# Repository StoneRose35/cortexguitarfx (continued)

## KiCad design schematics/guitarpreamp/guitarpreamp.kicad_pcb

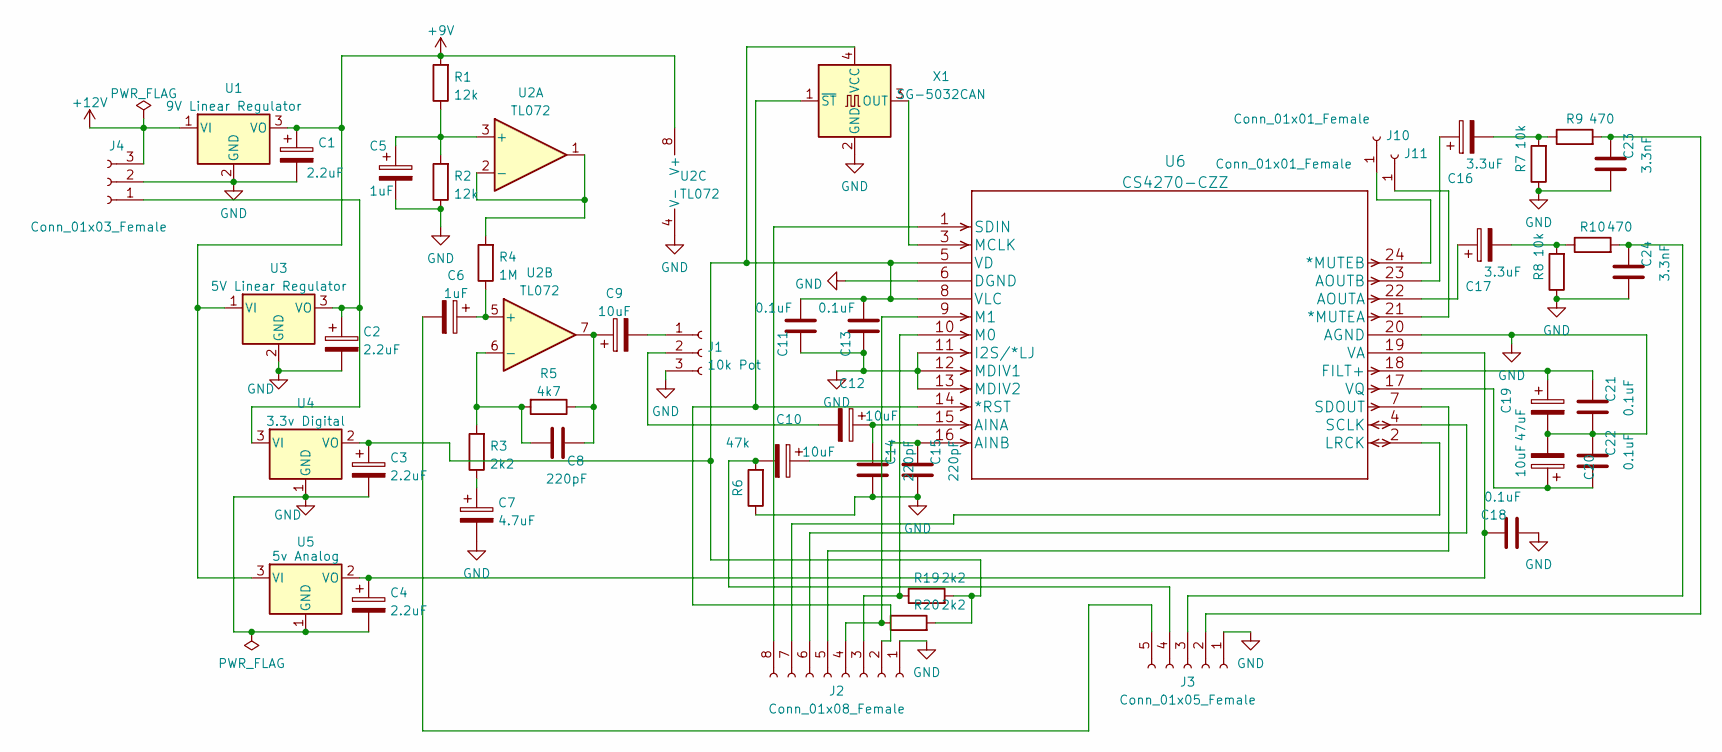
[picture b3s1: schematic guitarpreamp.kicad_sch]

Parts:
C1, C2, C3, C4: 2.2uF; CP_Elec_4x4.5
C5, C6: 1uF; CP_Elec_4x4.5
C7: 4.7uF; CP_Elec_4x4.5
C8, C14, C15: 220pF; C_0603_1608Metric_Pad1.08x0.95mm_HandSolder
C9, C10, C12, C20: 10uF; CP_Elec_4x4.5
C11, C13, C18, C21, C22: 0.1uF; C_1210_3225Metric_Pad1.33x2.70mm_HandSolder
C16, C17: 3.3uF; CP_Elec_4x4.5
C19: 47uF; CP_Elec_5x5.4
C23, C24: 3.3nF; C_0805_2012Metric_Pad1.18x1.45mm_HandSolder
J1: 10k Pot; PinHeader_1x03_P2.54mm_Vertical
J2: Conn_01x08_Female; PinHeader_1x08_P2.54mm_Vertical
J3: Conn_01x05_Female; PinHeader_1x05_P2.54mm_Vertical
J4: Conn_01x03_Female; PinHeader_1x03_P2.54mm_Vertical
J10, J11: Conn_01x01_Female; Pin_D0.7mm_L6.5mm_W1.8mm_FlatFork
R1, R2: 12k; R_0603_1608Metric_Pad0.98x0.95mm_HandSolder
R3, R19, R20: 2k2; R_0603_1608Metric_Pad0.98x0.95mm_HandSolder
R4: 1M; R_0603_1608Metric_Pad0.98x0.95mm_HandSolder
R5: 4k7; R_0603_1608Metric_Pad0.98x0.95mm_HandSolder
R6: 47k; R_0603_1608Metric_Pad0.98x0.95mm_HandSolder
R7, R8: 10k; R_0603_1608Metric_Pad0.98x0.95mm_HandSolder
R9, R10: 470; R_0603_1608Metric_Pad0.98x0.95mm_HandSolder
U1: 9V Linear Regulator; TO-252-2
U2: TL072; SOIC-8_3.9x4.9mm_P1.27mm
U3: 5V Linear Regulator; TO-252-2
U4: 3.3v Digital; SOT-23
U5: 5v Analog; SOT-23
U6: CS4270-CZZ; TSSOP-24_4.4x7.8mm_P0.65mm
X1: SG-5032CAN; Oscillator_SMD_SeikoEpson_SG8002CA-4Pin_7.0x5.0mm_HandSolde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

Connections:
+9V: C1.1, R1.2, U1.3 (VO), U2.8 (V+), U3.1 (VI), U5.3 (VI)
+12V: J4.3, U1.1 (VI)
GND: C1.2, C2.2, C3.2, C4.2, C5.2, C7.2, C11.2, C13.2, C14.1, C15.1, C18.1, C19.2, C20.2, C21.1, C22.2, C23.1, C24.1, J1.3, J2.1, J3.1, J4.2, R2.1, R6.1, R7.1, R8.1, U1.2 (GND), U2.4 (V-), U3.2 (GND), U4.1 (GND), U5.1 (GND), U6.6 (DGND), U6.11 (I2S/*LJ), U6.12 (MDIV1), U6.13 (MDIV2), U6.20 (AGND), X1.2 (GND)
unnamed: C2.1, J4.1, U3.3 (VO), U4.3 (VI)
unnamed: C5.1, R1.1, R2.2, U2.3 (+)
unnamed: C6.1, R4.1, U2.5 (+)
unnamed: C6.2, J3.5
unnamed: C7.1, R3.1
unnamed: C8.1, R3.2, R5.2, U2.6 (-)
unnamed: C8.2, C9.1, R5.1, U2.7
unnamed: C9.2, J1.1
unnamed: C10.1, C15.2, U6.16 (AINB)
unnamed: C10.2, J3.4, R6.2
unnamed: C3.1, C11.1, C13.1, R19.2, R20.2, U4.2 (VO), U6.5 (VD), U6.8 (VLC), X1.4 (VCC)
unnamed: C12.1, C14.2, U6.15 (AINA)
unnamed: C12.2, J1.2
unnamed: C16.1, U6.23 (AOUTB)
unnamed: C16.2, R7.2, R9.1
unnamed: C17.1, U6.22 (AOUTA)
unnamed: C17.2, R8.2, R10.1
unnamed: C4.1, C18.2, U5.2 (VO), U6.19 (VA)
unnamed: C19.1, C21.2, U6.18 (FILT+)
unnamed: C20.1, C22.1, U6.17 (VQ)
unnamed: C23.2, J3.2, R9.2
unnamed: C24.2, J3.3, R10.2
unnamed: J2.2, U6.14 (*RST), X1.1 (~ST)
unnamed: J2.3, R19.1, U6.10 (M0)
unnamed: J2.4, R20.1, U6.9 (M1)
unnamed: J2.5, U6.7 (SDOUT)
unnamed: J2.6, U6.4 (SCLK)
unnamed: J2.7, U6.2 (LRCK)
unnamed: J2.8, U6.1 (SDIN)
unnamed: J10.1, U6.24 (*MUTEB)
unnamed: J11.1, U6.21 (*MUTEA)
unnamed: R4.2, U2.1, U2.2 (-)
unnamed: U6.3 (MCLK), X1.3 (OUT)

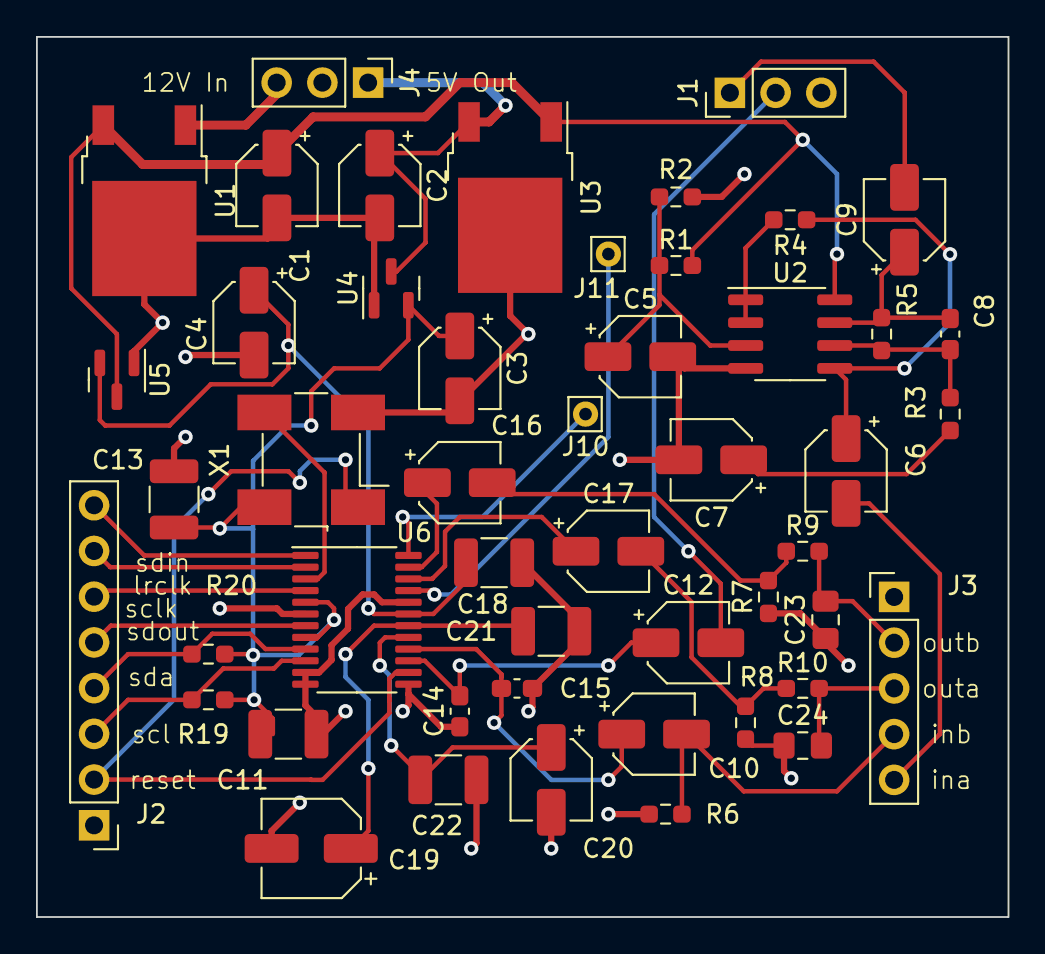
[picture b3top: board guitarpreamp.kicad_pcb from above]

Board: 2 copper layers, 54.0 x 48.9 mm, 49 parts (0 on the bottom side), 36 nets.

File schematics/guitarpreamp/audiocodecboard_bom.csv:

"Ref","Qnty","Value","Cmp name","Footprint","Description","Vendor"
"C1, C2, C3, C4, ","4","2.2uF","C_Polarized","Capacitor_SMD:CP_Elec_4x4.5","Polarized capacitor",""
"C5, C6, ","2","1uF","C_Polarized","Capacitor_SMD:CP_Elec_4x4.5","Polarized capacitor",""
"C7, ","1","4.7uF","C_Polarized","Capacitor_SMD:CP_Elec_4x4.5","Polarized capacitor",""
"C8, C14, C15, ","3","220pF","C","Capacitor_SMD:C_0603_1608Metric_Pad1.08x0.95mm_HandSolder","Unpolarized capacitor",""
"C9, C10, C12, C20, ","4","10uF","C_Polarized","Capacitor_SMD:CP_Elec_4x4.5","Polarized capacitor",""
"C11, C13, C18, C21, C22, ","5","0.1uF","C","Capacitor_SMD:C_1210_3225Metric_Pad1.33x2.70mm_HandSolder","Unpolarized capacitor",""
"C16, C17, ","2","3.3uF","C_Polarized","Capacitor_SMD:CP_Elec_4x4.5","Polarized capacitor",""
"C19, ","1","47uF","C_Polarized","Capacitor_SMD:CP_Elec_5x5.4","Polarized capacitor",""
"C23, C24, ","2","3.3nF","C","Capacitor_SMD:C_0805_2012Metric_Pad1.18x1.45mm_HandSolder","Unpolarized capacitor",""
"J1, ","1","10k Pot","Conn_01x03_Female","Connector_PinHeader_2.54mm:PinHeader_1x03_P2.54mm_Vertical","Generic connector, single row, 01x03, script generated (kicad-library-utils/schlib/autogen/connector/)",""
"J2, ","1","Conn_01x08_Female","Conn_01x08_Female","Connector_PinHeader_2.54mm:PinHeader_1x08_P2.54mm_Vertical","Generic connector, single row, 01x08, script generated (kicad-library-utils/schlib/autogen/connector/)",""
"J3, ","1","Conn_01x05_Female","Conn_01x05_Female","Connector_PinHeader_2.54mm:PinHeader_1x05_P2.54mm_Vertical","Generic connector, single row, 01x05, script generated (kicad-library-utils/schlib/autogen/connector/)",""
"J4, ","1","Conn_01x03_Female","Conn_01x03_Female","Connector_PinHeader_2.54mm:PinHeader_1x03_P2.54mm_Vertical","Generic connector, single row, 01x03, script generated (kicad-library-utils/schlib/autogen/connector/)",""
"J10, J11, ","2","Conn_01x01_Female","Conn_01x01_Female","Connector_Pin:Pin_D0.7mm_L6.5mm_W1.8mm_FlatFork","Generic connector, single row, 01x01, script generated (kicad-library-utils/schlib/autogen/connector/)",""
"R1, R2, ","2","12k","R","Resistor_SMD:R_0603_1608Metric_Pad0.98x0.95mm_HandSolder","Resistor",""
"R3, R19, R20, ","3","2k2","R","Resistor_SMD:R_0603_1608Metric_Pad0.98x0.95mm_HandSolder","Resistor",""
"R4, ","1","1M","R","Resistor_SMD:R_0603_1608Metric_Pad0.98x0.95mm_HandSolder","Resistor",""
"R5, ","1","4k7","R","Resistor_SMD:R_0603_1608Metric_Pad0.98x0.95mm_HandSolder","Resistor",""
"R6, ","1","47k","R","Resistor_SMD:R_0603_1608Metric_Pad0.98x0.95mm_HandSolder","Resistor",""
"R7, R8, ","2","10k","R","Resistor_SMD:R_0603_1608Metric_Pad0.98x0.95mm_HandSolder","Resistor",""
"R9, R10, ","2","470","R","Resistor_SMD:R_0603_1608Metric_Pad0.98x0.95mm_HandSolder","Resistor",""
"U1, ","1","9V Linear Regulator","LM78M05_TO252","Package_TO_SOT_SMD:TO-252-2","Positive 500mA 35V Linear Regulator, Fixed Output 5V, TO-252 (D-PAK)",""
"U2, ","1","TL072","TL072","Package_SO:SOIC-8_3.9x4.9mm_P1.27mm","Dual Low-Noise JFET-Input Operational Amplifiers, DIP-8/SOIC-8",""
"U3, ","1","5V Linear Regulator","LM78M05_TO252","Package_TO_SOT_SMD:TO-252-2","Positive 500mA 35V Linear Regulator, Fixed Output 5V, TO-252 (D-PAK)",""
"U4, ","1","3.3v Digital","MCP1700-1202E_SOT23","Package_TO_SOT_SMD:SOT-23","250mA Low Quiscent Current LDO, 1.2V output, SOT-23",""
"U5, ","1","5v Analog","MCP1700-1202E_SOT23","Package_TO_SOT_SMD:SOT-23","250mA Low Quiscent Current LDO, 1.2V output, SOT-23",""
"U6, ","1","CS4270-CZZ","CS4270-CZZ","Package_SO:TSSOP-24_4.4x7.8mm_P0.65mm","",""
"X1, ","1","SG-5032CAN","SG-5032CAN","Oscillator:Oscillator_SMD_SeikoEpson_SG8002CA-4Pin_7.0x5.0mm_HandSoldering","CMOS Clock Oscillator 1 to 75 MHz",""

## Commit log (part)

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2023-11-13 (hopefully) corrected level 2 layout
2023-11-14 increased initial delay for simple chorus
2023-11-14 fixed acoustic processor and included it
    instead of the mostercrusher
2023-11-17 fixed display error in ui lvl 1 and 2
2023-11-20 re-added component values previously lost due to kicad mishap
2023-11-23 more rearranging includes
2023-11-23 added about display
2023-11-23 changed config for pipico fx stomp
2023-11-24 reduced #samples per parameter @ integration tests
2023-11-26 makefile changes
    changed project name and encoded version
    in the name of the binary
2023-11-26 schematics
    adjusted track widths
2023-11-30 pcb: layout changes, c headers: documentation
2024-02-07 fixed layout error, added copper fill
2024-02-08 pitchshifter done
2024-02-24 added decoupling caps at mic input
2024-02-25 memory rearranging (WIP)
2024-02-26 new kicad project for a board compatible with various dev boards
2024-03-02 added adapter board for raspberryy pi pico
2024-03-03 trying corrected bias issues in waveshaper
2024-03-03 WIP: driver for external codec
2024-03-03 completed pin mapping for seed
2024-03-03 daisy seed adapter board: initial layout
2024-03-04 correct codec sdin and sdout directions
2024-03-07 rescue boot option
2024-03-07 added driver includes
2024-03-10 moved functions to qspi
2024-03-10 wip: port fir and first order iir filters
2024-03-10 wip: ported reverb
2024-03-11 wip: more ports, all audio block and programs 1-4
2024-03-14 wip: proting existing programs done, linking errors remain
2024-03-14 wip: added parts of the ui, missing: stomp switches drivers, additional fx programs
2024-03-16 everything ported, ready to debug
2024-03-17 WORKS: display and encoder issues fixed
2024-03-19 DONE: checked&corrected every fx program
2024-03-21 crucial bugfixes
    * inline clip-function
    * adc work now truly synchronized and double-buffered
2024-05-04 corrected delay time/decay calculation for reverb
2024-05-05 correction: taking delay length dependent feedbacks into consideration
2024-05-09 finally fixed the issue of output and input levels being erroneously equal
2024-06-18 corrected compressor makeup gain
2024-09-18 more work on full schematic: added test points
2025-02-18 finally fixed unintentional overflow due to summing up both channels
2025-02-18 schematics changed and added gitignore files
2025-02-18 added a few testpoints
2025-02-27 a new effect: Shimmer Reverb, still needs a lot of tweaking though
2025-03-05 pitchshifter and shimmerreverb: added second pitchshifter algorithm, improved and audio-tested (simulator and hardware) the shimmer reverb
2025-03-10 included full driver for the pcm3060 audio codec and made codec choice configurable
2025-03-10 added gitignore
2025-03-10 spreadsheet for claculating phase distortion
2025-03-13 added tremolo program
2025-03-14 corrected and trimmed tremolo
2025-03-22 corrected wiring mistake found during hw test of first batch
2025-03-23 corrected i2c address for pcm3060
2025-03-23 exchanged incorrect pcm3060 symbol, cleaned symbol table
2025-03-29 added specific program for performing hardware checks
2025-03-29 organized various compilation options as preprocessor directives, made USB over UART configurable at compile time
2025-03-29 added svd to project
2025-03-30 minor changes and corrections
2025-03-31 added display driver for dogm128 module, minor fixes along the way
2025-04-04 added extension board code, reorganized configs and added input clipping indication
2025-04-06 USB: first signs of life!
2025-04-07 more usb driver done
2025-04-12 USB: Enumeration works!
2025-04-15 USB CDC driver working!
2025-04-15 removed unused libs
2025-04-17 memory rearrangement, pt 2
2025-04-17 minor corrections and fixes
2025-04-17 i2c driver fix, pt 2
2025-04-17 work in progress: fw upgrade via usb
2025-04-23 switching presets taken from rp2040_stomp
2025-04-23 got rid of i2c polling (only stm32 part so far)
2025-04-24 bugfix
2025-04-25 updated atmega88 firmware for multi-master communication
2025-04-25 added config for avr gcc
2025-04-25 multi-master i2c done!
2025-04-25 removed commented and unused section
2025-04-30 usb: integrated usb dfu driver and checked usb enumeration and configuration
2025-04-30 cosmetic..
2025-05-04 command line tool to generated a dfu-file containing flash and qspi binary
2025-05-04 corrected flow control auf the audio engine, no waits in interrupt handler anymore!
2025-05-06 dogm display driver tested and corrected, works now!
2025-05-11 testable footdrum sample player done
2025-05-13 footdrums fully functional!
2025-05-17 flipped edge of switch, tidying
2025-05-20 tested and fixed clock increase to 200 MHz
2025-05-20 tidied clcok freq calculation scripts
2025-05-24 various stuff
    * moved functions to sram since flash access is now substantially slower compared to sram (flash acces division is now four because of the cpu running at 200 MHz
    * forgotten commit of the few previous commits
2025-05-29 bugfix saving presets & cleanup
2025-06-06 Flash erase/write functionalities put together and some corrections along the way
2025-06-10 dfu uploader: initial state
2025-06-15 dfu simulated&debugged
    * added sim mode for dfu
    * debugged dfu programming
    * included bin2dfu in makefile
2025-06-22 fix for a really stupid bug :-/
2025-06-26 bugfix, don't return with code 1 when right at end
2025-06-27 wip: web usb for firmware uploading
2025-07-01 web usb firmware upgrade continued
2025-07-04 cleanup and tuning
2025-07-04 added a volume parameter to each fx program
2025-07-06 finxed, the bitcrusher, finally!
2025-07-06 missed change in "fixed the bitbrusher...)
2025-07-07 tested&added freeverb, alon gwith some small improvements
2025-07-07 tuned/fixed sine chorus, does now also produce flanger-like sound
2025-07-10 started moving fx program to c++
2025-07-10 little corrections
2025-07-13 formal split into c++ done, remaining * fill in functionality for fx froms 4 to 16 * soft-swap of fx programs * proper destruction / handling delay memory pointers
2025-08-03 migration to c++ ready to be tested!
2025-08-17 separate systick counter for core 1
2025-08-21 extensive testing and debugging the cpp version
2025-08-26 minor changes
2025-09-22 changed display driver
2025-09-25 fixed dogmw128: added waits, parametrizable support for flipped display
2025-09-25 FORCE_TEST_MODE compiles again
2025-09-25 removed obious bug in system settings page
2025-10-07 updated bom
2025-10-10 migration to c++ done
    also added shimmerverb, tremolo and freeverb from the pipico-version
    many little corrections along the way
2025-10-10 moved some code to qspi memory, now also compiles against external pcm3060 codec
2025-10-19 properly handled audio codec types via preprocessor directives
2025-10-19 graphics and display: various small improvements
2025-10-19 properly handled audio codecs using defines
2025-10-19 increased heap and stack
2025-10-22 (greatly) optimized memory allocation with respect to distribution and performance
2025-10-23 added mcu board to build info
2025-10-23 prepared for compilation using optimization, fixed bug found that way
2025-10-23 minimal consistency check to avoid running into problems later..
2025-10-23 added consistency check and fixed error occured because of not having it beforehand
2025-10-23 removed or commented usused code, small bug fixes
2025-10-24 many samll fixed adopted from the daisySeed-branch
2025-10-24 various changes: Correct regarding display and state of parameters, automatically restart after flashing the qspi bugfix:freeze when changing to preset mode
2025-10-24 fixed negative offset in bitcrusher
2025-10-27 implemented sync scheme to be able to do the firmware upgrade using stlink in one go
2025-10-27 added mpu (and icache&dcache in an earlier commit)
2025-10-29 small tweaks and and fix of error in program0 and systemsettings
2025-10-30 common stability and functionality improvement adopted from daisySeed-branch
2025-10-31 more minor performance improvements and ui fixes
2025-11-04 UI fixes: Changing presets on same stomp switch works when changing banks settings start with volume 100%, initial program is "off"
2025-11-04 implemented rotary encoder with speed measurement
2025-11-06 V0.8: added looper functionality
2025-11-07 remaining part of the one-click build,deploy&debug capability
2025-11-09 [Cherry] Preset preview when switching banks
2025-11-09 improved rotary encoder driver: speedup is now more pronounced, encoder is less glitchy also
2025-11-09 better rotary encoder speed handling
2025-11-09 better rotary encoder speed handling, part 2
2025-11-09 adapted and corrected preset preview
2025-11-11 rotary encoder slowdown in string editor
2025-11-19 added capability to program the extension board firmware from the core, allows to include firmware updates for the extension board in the uf2/dfu file, eliminates the need to flash the atmega using a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
2025-11-19 avr flasher: schematic changes
2025-12-23 avr programmer working!
2025-12-26 added preprocessor flag for avr programmer
2025-12-28 implemented a multimode filter * maths: exponential function and test for it * fixed offline processor and tidied includes
2025-12-28 ignore more generated content
2025-12-28 ..just uploads the firmware to an avr on button presses
2026-01-01 avr programmer for atmega8 working
2026-01-03 minor things
2026-01-12 added basic 4*4 matrix functions
2026-01-15 added generic distortion curve
2026-01-21 corrected and field-proofed actual firmware update via usb
2026-01-25 added bresenhams linedrawing algo
2026-01-25 moved more ui code into qspi flash
2026-01-25 changed version nr and project name for the tag
2026-01-25 added another utility for first-time flashing the daisy seed board over usb
2026-01-28 switched back to spi commands for flashing since qpi command din't seem to work so far
2026-02-04 firmware web flasher is finally useable and understandeable
2026-02-04 extracted version number to usb descriptors and file names
2026-02-05 fixed line drawing algorithm
2026-02-07 corrected debug task for bins2dfu
2026-02-08 More bugfixes regarding dfu
2026-02-08 added simpler piecewise linear distortion curve
2026-02-12 added image assets
2026-02-12 build infrastructure:removed errouneous check which resulte in a dfu error state, defined dfu as a standard upload method
2026-02-20 implemented on/off switching capabilities on all, freeze on delay and reverb,
2026-02-20 mostly corrections resulting from pedantic compilation settings
2026-02-20 remove unused
2026-02-20 more tests...
2026-02-25 gradually changing freezer state to avoid clicks when freezing delay and reverb
2026-02-26 merged ui overhaul and copy/swap/delete functionality from daisy seed branch
2026-03-01 bugfixed and treated pedantic warnings
2026-03-02 pedantic warnings...
2026-03-03 corrected behaviour of reverb2 and reverb3
2026-03-05 removed some backup schematics
2026-03-20 major change: multiple effect loadable with flexible routing
2026-03-27 large ui overhaul (unfinished) * set up bottom panel * added images * implemented stomp box mode * few basic checks done
2026-04-09 removed a whole lotta logical errors..
2026-04-19 refined param edit, now knobs become active when moving over a parameter
2026-04-19 added calibration for adc's improving the range
2026-04-23 added smulator to render ui image to bitmap ... for creating a manual
2026-04-25 copying preset tested&working
2026-04-25 slightly moving a knob selects the parameter
2026-04-26 many small ui fixed * enter&stompswitch from pedalboard to respective fx program works reliably * routing is stored in preset * routing 2p_s sounds as expected ... more minor things
2026-04-30 usb driver fixed, sending over usb works
2026-05-10 firmware upgrade: don't forget usb devices if already connected once
2026-05-16 bugfix ins usb driver: sending also work for endpoints other than nr0
2026-05-16 basic tech breakthrough of web editor done, basic layout of web editor done and started interface documentation
2026-05-17 implemented synchronizing fx programs with the web editor
2026-05-25 more webapp done,
